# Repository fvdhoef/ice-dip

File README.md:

# ICE-DIP

Designed by Frank van den Hoef in 2021.

This is a small FPGA board containing the Lattice iCE40 UltraPlus 5K FPGA. 

NOTE: At this moment this design is untested.

## Features
- Lattice ICE40UP5K-SG48I FPGA, 5K logic elements, 15KB+128KB embedded block RAM
- DIP40 form factor with machined pin headers for easy integration in retro computer designs.
- Level translating bus switches on all I/O pins to allow interfacing with 5V logic. (NOTE: output levels will still be max 3.3V)
- 2MB SPI flash for 1 to 4 configuration images.
- On-board crystal oscillator.
- On-board power supplies for 3.3V and 1.2V.
- Open-source hardware. [Schematic](pcb/ice-dip-schematic.pdf) and layout (in KiCad format) are free for you to use and modify.

## Renders

## Downloads
- [Schematic](pcb/ice-dip-schematic.pdf)
- [Bill of Materials](pcb/ice-dip-bom.csv)
- [Gerbers files](pcb/ice-dip-gerbers.zip)

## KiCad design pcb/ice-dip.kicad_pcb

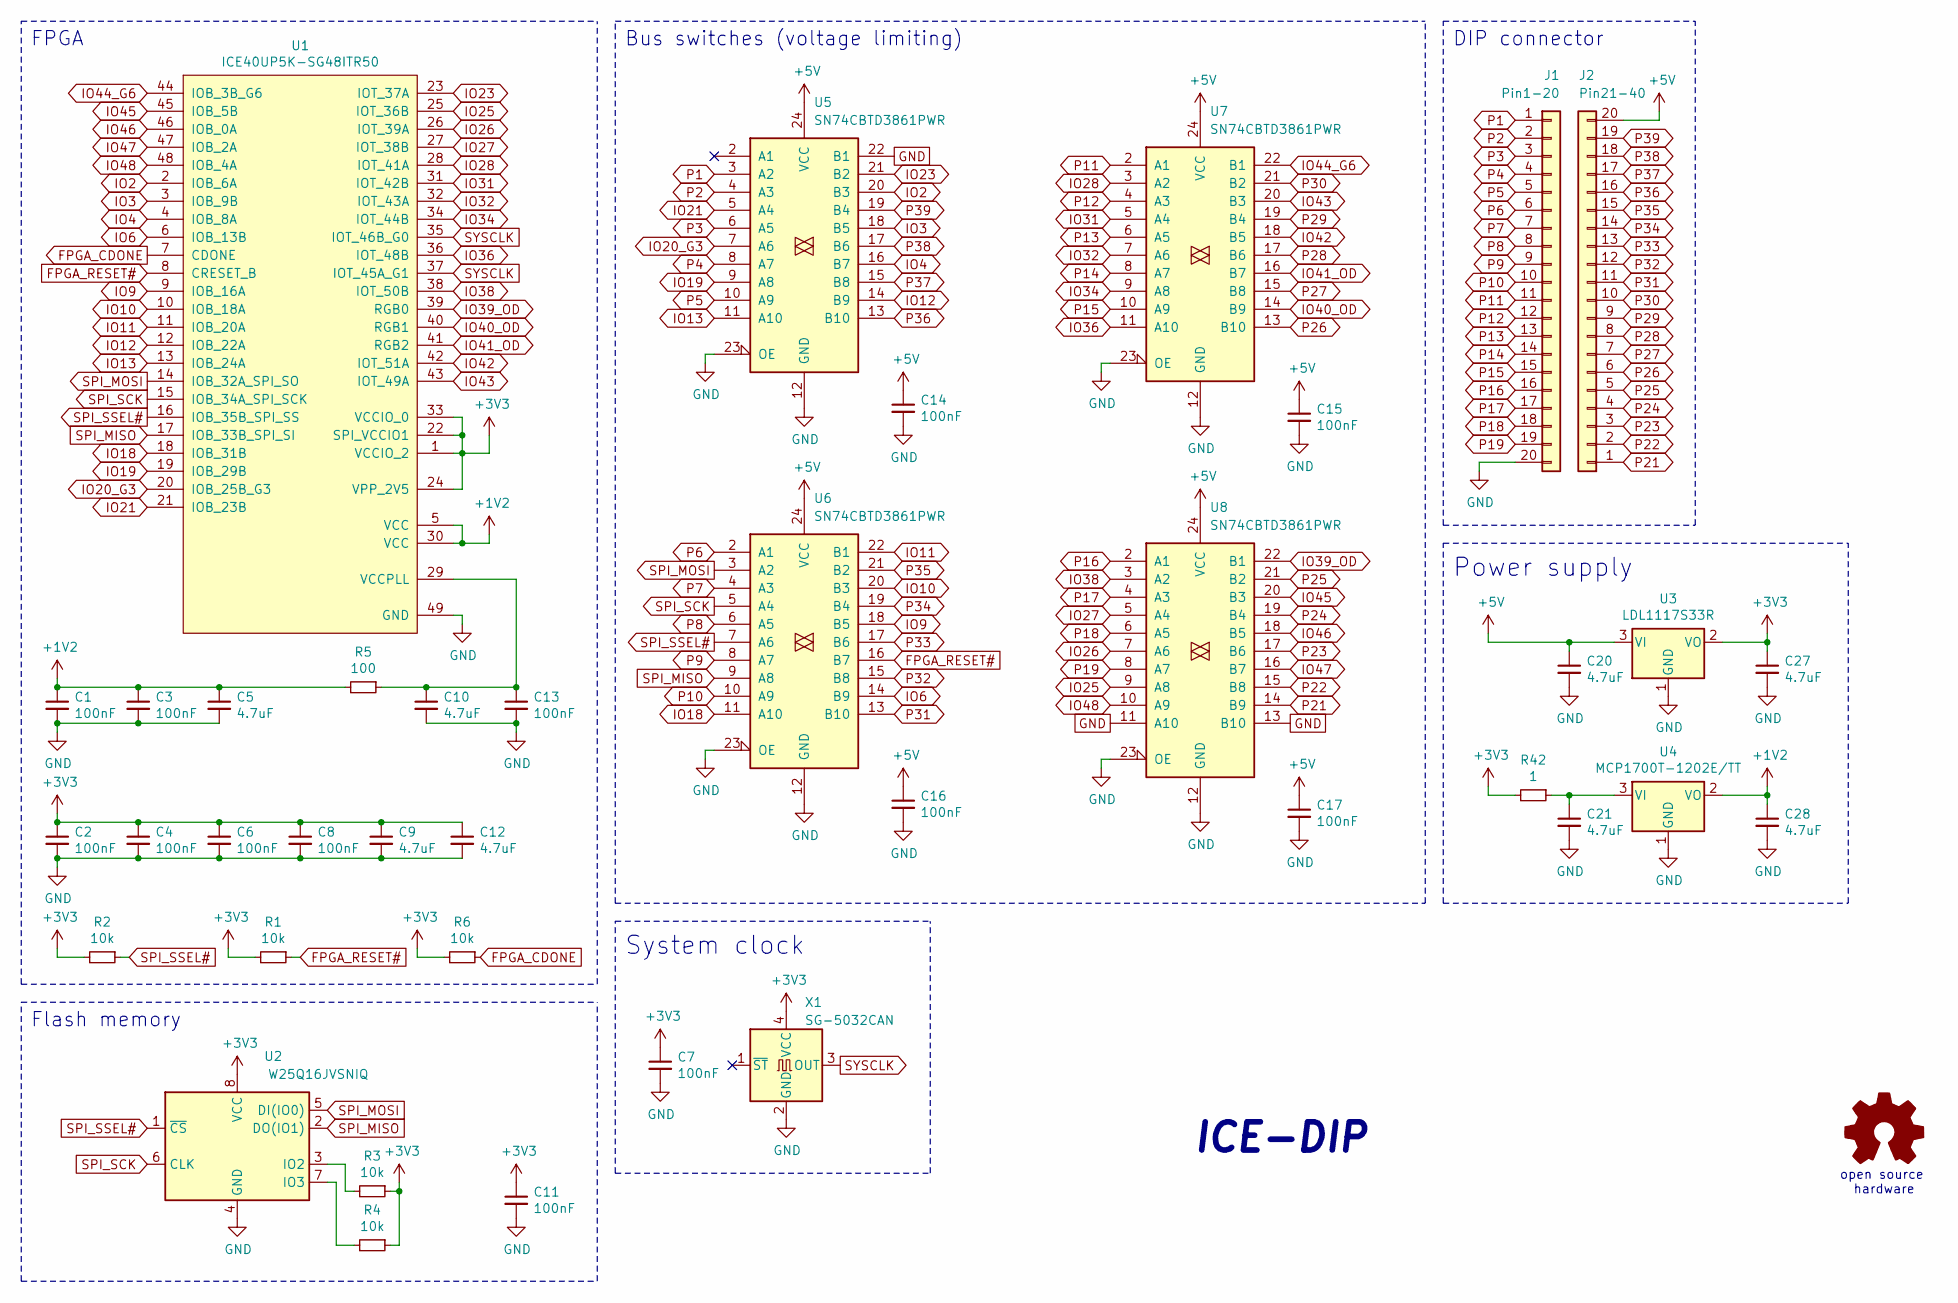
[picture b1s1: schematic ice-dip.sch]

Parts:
C1, C2, C3, C4, C6, C7, C8, C11, C13, C14, C15, C16, C17: 100nF; C_0603_1608Metric
C5, C9, C10, C12, C20, C21, C27, C28: 4.7uF; C_0603_1608Metric
J1: Pin1-20; PinHeader_1x20_P2.54mm_Vertical
J2: Pin21-40; PinHeader_1x20_P2.54mm_Vertical
LOGO1: Logo_Open_Hardware_Small; OSHW-Logo_7.5x8mm_SilkScreen
R1, R2, R3, R4, R6: 10k; R_0603_1608Metric
R5: 100; R_0603_1608Metric
R42: 1; R_0603_1608Metric
U1: ICE40UP5K-SG48ITR50; QFN-48-1EP_7x7mm_P0.5mm_EP5.3x5.3mm
U2: W25Q16JVSNIQ; SOIC-8_3.9x4.9mm_P1.27mm
U3: LDL1117S33R; SOT-223-3_TabPin2
U4: MCP1700T-1202E/TT; SOT-23
U5, U6, U7, U8: SN74CBTD3861PWR; TSSOP-24_4.4x7.8mm_P0.65mm
X1: SG-5032CAN; Oscillator_SMD_SeikoEpson_SG8002LB-4Pin_5.0x3.2mm

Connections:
+1V2: C1.1, C3.1, C5.1, C28.1, R5.2, U1.5 (VCC), U1.30 (VCC), U4.2 (VO)
+3V3: C2.1, C4.1, C6.1, C7.1, C8.1, C9.1, C11.1, C12.1, C27.1, R1.2, R2.2, R3.1, R4.1, R6.2, R42.2, U1.1 (VCCIO_2), U1.22 (SPI_VCCIO1), U1.24 (VPP_2V5), U1.33 (VCCIO_0), U2.8 (VCC), U3.2 (VO), X1.4 (VCC)
+5V: C14.1, C15.1, C16.1, C17.1, C20.1, J2.20, U3.3 (VI), U5.24 (VCC), U6.24 (VCC), U7.24 (VCC), U8.24 (VCC)
FPGA_CDONE: R6.1, U1.7 (CDONE)
FPGA_RESET#: R1.1, U1.8 (CRESET_B), U6.16 (B7)
GND: C1.2, C2.2, C3.2, C4.2, C5.2, C6.2, C7.2, C8.2, C9.2, C10.2, C11.2, C12.2, C13.2, C14.2, C15.2, C16.2, C17.2, C20.2, C21.2, C27.2, C28.2, J1.20, U1.49 (GND), U2.4 (GND), U3.1 (GND), U4.1 (GND), U5.12 (GND), U5.22 (B1), U5.23 (OE), U6.12 (GND), U6.23 (OE), U7.12 (GND), U7.23 (OE), U8.11 (A10), U8.12 (GND), U8.13 (B10), U8.23 (OE), X1.2 (GND)
IO2: U1.2 (IOB_6A), U5.20 (B3)
IO3: U1.3 (IOB_9B), U5.18 (B5)
IO4: U1.4 (IOB_8A), U5.16 (B7)
IO6: U1.6 (IOB_13B), U6.14 (B9)
IO9: U1.9 (IOB_16A), U6.18 (B5)
IO10: U1.10 (IOB_18A), U6.20 (B3)
IO11: U1.11 (IOB_20A), U6.22 (B1)
IO12: U1.12 (IOB_22A), U5.14 (B9)
IO13: U1.13 (IOB_24A), U5.11 (A10)
IO18: U1.18 (IOB_31B), U6.11 (A10)
IO19: U1.19 (IOB_29B), U5.9 (A8)
IO20_G3: U1.20 (IOB_25B_G3), U5.7 (A6)
IO21: U1.21 (IOB_23B), U5.5 (A4)
IO23: U1.23 (IOT_37A), U5.21 (B2)
IO25: U1.25 (IOT_36B), U8.9 (A8)
IO26: U1.26 (IOT_39A), U8.7 (A6)
IO27: U1.27 (IOT_38B), U8.5 (A4)
IO28: U1.28 (IOT_41A), U7.3 (A2)
IO31: U1.31 (IOT_42B), U7.5 (A4)
IO32: U1.32 (IOT_43A), U7.7 (A6)
IO34: U1.34 (IOT_44B), U7.9 (A8)
IO36: U1.36 (IOT_48B), U7.11 (A10)
IO38: U1.38 (IOT_50B), U8.3 (A2)
IO39_OD: U1.39 (RGB0), U8.22 (B1)
IO40_OD: U1.40 (RGB1), U7.14 (B9)
IO41_OD: U1.41 (RGB2), U7.16 (B7)
IO42: U1.42 (IOT_51A), U7.18 (B5)
IO43: U1.43 (IOT_49A), U7.20 (B3)
IO44_G6: U1.44 (IOB_3B_G6), U7.22 (B1)
IO45: U1.45 (IOB_5B), U8.20 (B3)
IO46: U1.46 (IOB_0A), U8.18 (B5)
IO47: U1.47 (IOB_2A), U8.16 (B7)
IO48: U1.48 (IOB_4A), U8.10 (A9)
unnamed: C10.1, C13.1, R5.1, U1.29 (VCCPLL)
unnamed: C21.1, R42.1, U4.3 (VI)
unnamed: R3.2, U2.3 (IO2)
unnamed: R4.2, U2.7 (IO3)
P1: J1.1, U5.3 (A2)
P2: J1.2, U5.4 (A3)
P3: J1.3, U5.6 (A5)
P4: J1.4, U5.8 (A7)
P5: J1.5, U5.10 (A9)
P6: J1.6, U6.2 (A1)
P7: J1.7, U6.4 (A3)
P8: J1.8, U6.6 (A5)
P9: J1.9, U6.8 (A7)
P10: J1.10, U6.10 (A9)
P11: J1.11, U7.2 (A1)
P12: J1.12, U7.4 (A3)
P13: J1.13, U7.6 (A5)
P14: J1.14, U7.8 (A7)
P15: J1.15, U7.10 (A9)
P16: J1.16, U8.2 (A1)
P17: J1.17, U8.4 (A3)
P18: J1.18, U8.6 (A5)
P19: J1.19, U8.8 (A7)
P21: J2.1, U8.14 (B9)
P22: J2.2, U8.15 (B8)
P23: J2.3, U8.17 (B6)
P24: J2.4, U8.19 (B4)
P25: J2.5, U8.21 (B2)
P26: J2.6, U7.13 (B10)
P27: J2.7, U7.15 (B8)
P28: J2.8, U7.17 (B6)
P29: J2.9, U7.19 (B4)
P30: J2.10, U7.21 (B2)
P31: J2.11, U6.13 (B10)
P32: J2.12, U6.15 (B8)
P33: J2.13, U6.17 (B6)
P34: J2.14, U6.19 (B4)
P35: J2.15, U6.21 (B2)
P36: J2.16, U5.13 (B10)
P37: J2.17, U5.15 (B8)
P38: J2.18, U5.17 (B6)
P39: J2.19, U5.19 (B4)
SPI_MISO: U1.17 (IOB_33B_SPI_SI), U2.2 (DO(IO1)), U6.9 (A8)
SPI_MOSI: U1.14 (IOB_32A_SPI_SO), U2.5 (DI(IO0)), U6.3 (A2)
SPI_SCK: U1.15 (IOB_34A_SPI_SCK), U2.6 (CLK), U6.5 (A4)
SPI_SSEL#: R2.1, U1.16 (IOB_35B_SPI_SS), U2.1 (~CS), U6.7 (A6)
SYSCLK: U1.35 (IOT_46B_G0), U1.37 (IOT_45A_G1), X1.3 (OUT)

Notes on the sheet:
FPGA
Flash memory
Power supply
Bus switches (voltage limiting)
DIP connector
System clock
open source hardware
ICE-DIP

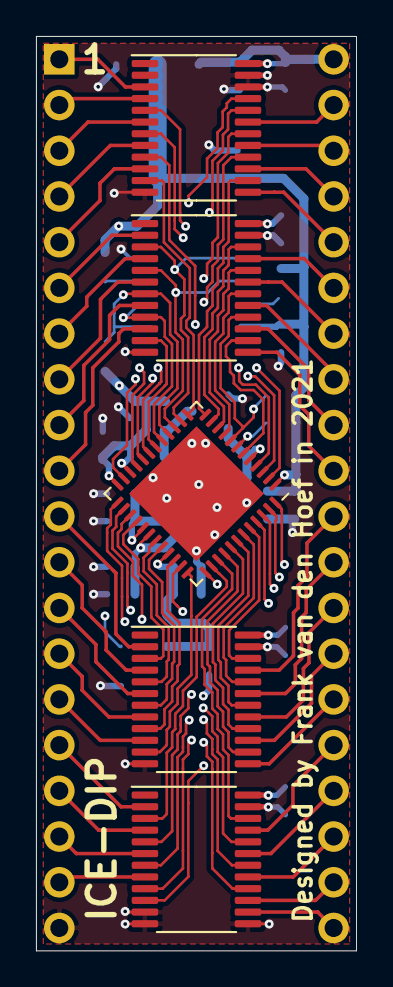
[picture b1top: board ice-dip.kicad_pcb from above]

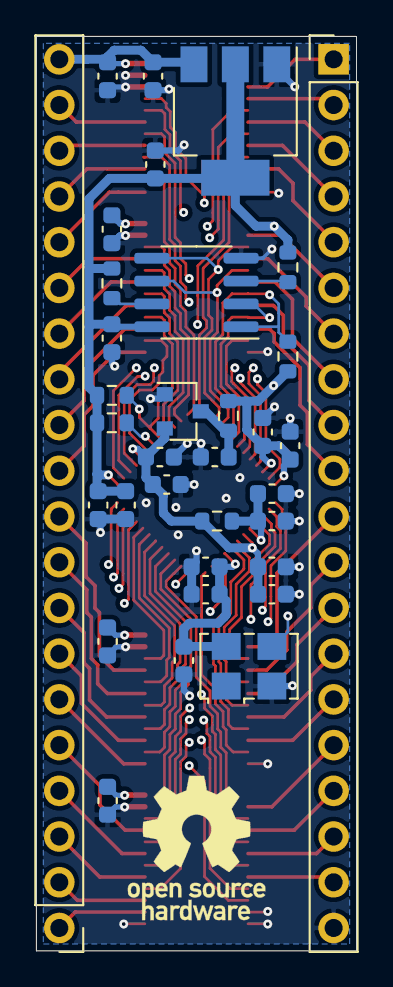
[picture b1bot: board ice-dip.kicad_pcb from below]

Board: 4 copper layers, 17.8 x 50.8 mm, 40 parts (35 on the bottom side), 86 nets.

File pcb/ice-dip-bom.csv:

Quantity;Value;Footprint;Refs
13;100nF;C0603 X5R/X7R;C1, C2, C3, C4, C6, C7, C8, C11, C13, C14, C15, C16, C17
8;4.7uF;C0603 X5R/X7R;C5, C9, C10, C12, C20, C21, C27, C28
;;;
1;1;R0603;R42
1;100;R0603;R5
5;10k;R0603;R1, R2, R3, R4, R6
;;;
1;SG-5032CAN;Oscillator 5.0x3.2mm;X1
;;;
1;ICE40UP5K-SG48ITR50;QFN-48-1EP_7x7mm_P0.5mm_EP5.3x5.3mm;U1
1;W25Q16JVSNIQ;SOIC-8_3.9x4.9mm_P1.27mm;U2
4;SN74CBTD3861PWR;TSSOP-24_4.4x7.8mm_P0.65mm;U5, U6, U7, U8
1;LDL1117S33R;SOT-223-3_TabPin2;U3
1;MCP1700T-1202E/TT;SOT-23;U4
;;;
2;Pin1-20, Pin21-40;Samtec TS-120-T-A;J1, J2

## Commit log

2021-10-26 Initial commit.
2021-10-26 Added initial README and images.
2021-10-26 Image side-by-side.
2021-10-26 Images side by side.
2021-10-26 Updated README.
2021-10-26 Added schematic in PDF format.
2021-10-27 Library for ICE-DIP component. Fixing some small issues.
2021-10-27 Updating schematic.
2021-10-27 Added extra copper pours. Added gerbers + bill of materials.
